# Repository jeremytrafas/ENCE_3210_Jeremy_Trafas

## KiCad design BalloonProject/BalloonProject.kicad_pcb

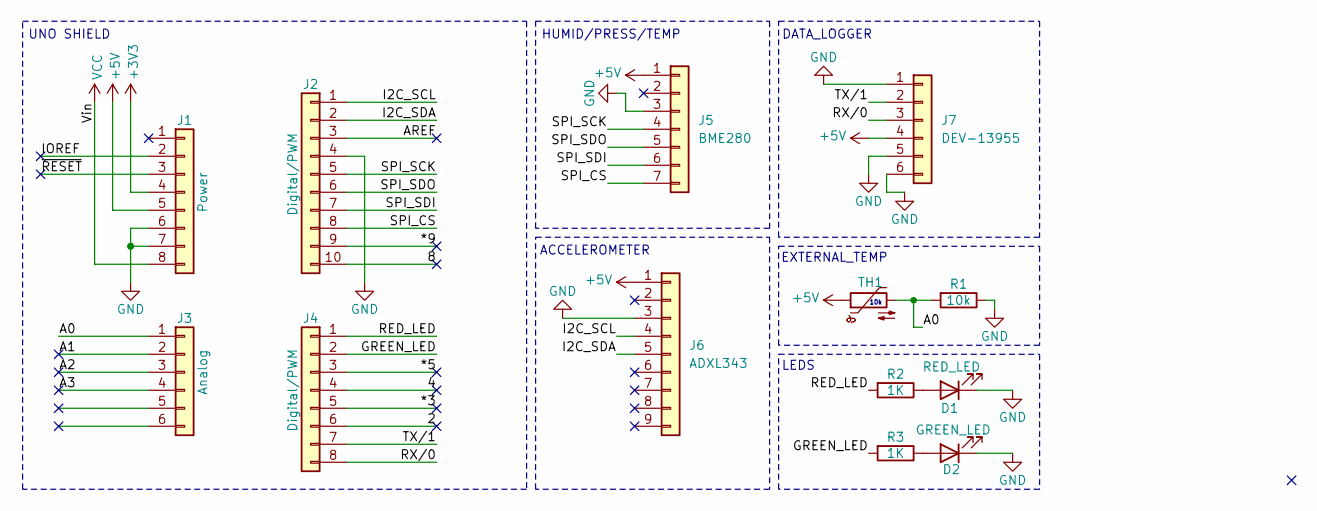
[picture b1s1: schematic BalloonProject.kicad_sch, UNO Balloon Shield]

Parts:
D1: RED_LED; LED_D5.0mm
D2: GREEN_LED; LED_D5.0mm
J1: Power; PinSocket_1x08_P2.54mm_Vertical
J2: Digital/PWM; PinSocket_1x10_P2.54mm_Vertical
J3: Analog; PinSocket_1x06_P2.54mm_Vertical
J4: Digital/PWM; PinSocket_1x08_P2.54mm_Vertical
J5: BME280; PinSocket_1x07_P2.54mm_Vertical
J6: ADXL343; PinSocket_1x09_P2.54mm_Vertical
J7: DEV-13955; PinSocket_1x06_P2.54mm_Vertical
NXRT15XH103FA1B030: TH1; R_Axial_DIN0411_L9.9mm_D3.6mm_P15.24mm_Horizontal
R1: 10k; R_Axial_DIN0411_L9.9mm_D3.6mm_P15.24mm_Horizontal
R2, R3: 1K; R_Axial_DIN0411_L9.9mm_D3.6mm_P15.24mm_Horizontal

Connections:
+3V3: J1.4
+5V: J1.5, J5.1, J6.1, J7.4, NXRT15XH103FA1B030.1
/2: J4.6
/4: J4.4
/8: J2.10
/*3: J4.5
/*5: J4.3
/*9: J2.9
/A0: J3.1, NXRT15XH103FA1B030.2, R1.2
/A1: J3.2
/A2: J3.3
/A3: J3.4
/AREF: J2.3
/GREEN_LED: J4.2, R3.2
/I2C_SCL: J2.1, J6.4
/I2C_SDA: J2.2, J6.5
/IOREF: J1.2
/RED_LED: J4.1, R2.2
/RX/0: J4.8, J7.3
/SPI_CS: J2.8, J5.7
/SPI_SCK: J2.5, J5.4
/SPI_SDI: J2.7, J5.6
/SPI_SDO: J2.6, J5.5
/TX/1: J4.7, J7.2
/~RESET: J1.3
GND: D1.1 (K), D2.1 (K), J1.6, J1.7, J2.4, J5.3, J6.3, J7.1, J7.5, J7.6, R1.1
unnamed: D1.2 (A), R2.1
unnamed: D2.2 (A), R3.1
VCC: J1.8

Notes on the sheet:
10k
ACCELEROMETER
UNO SHIELD
LEDS
HUMID/PRESS/TEMP
EXTERNAL_TEMP
DATA_LOGGER

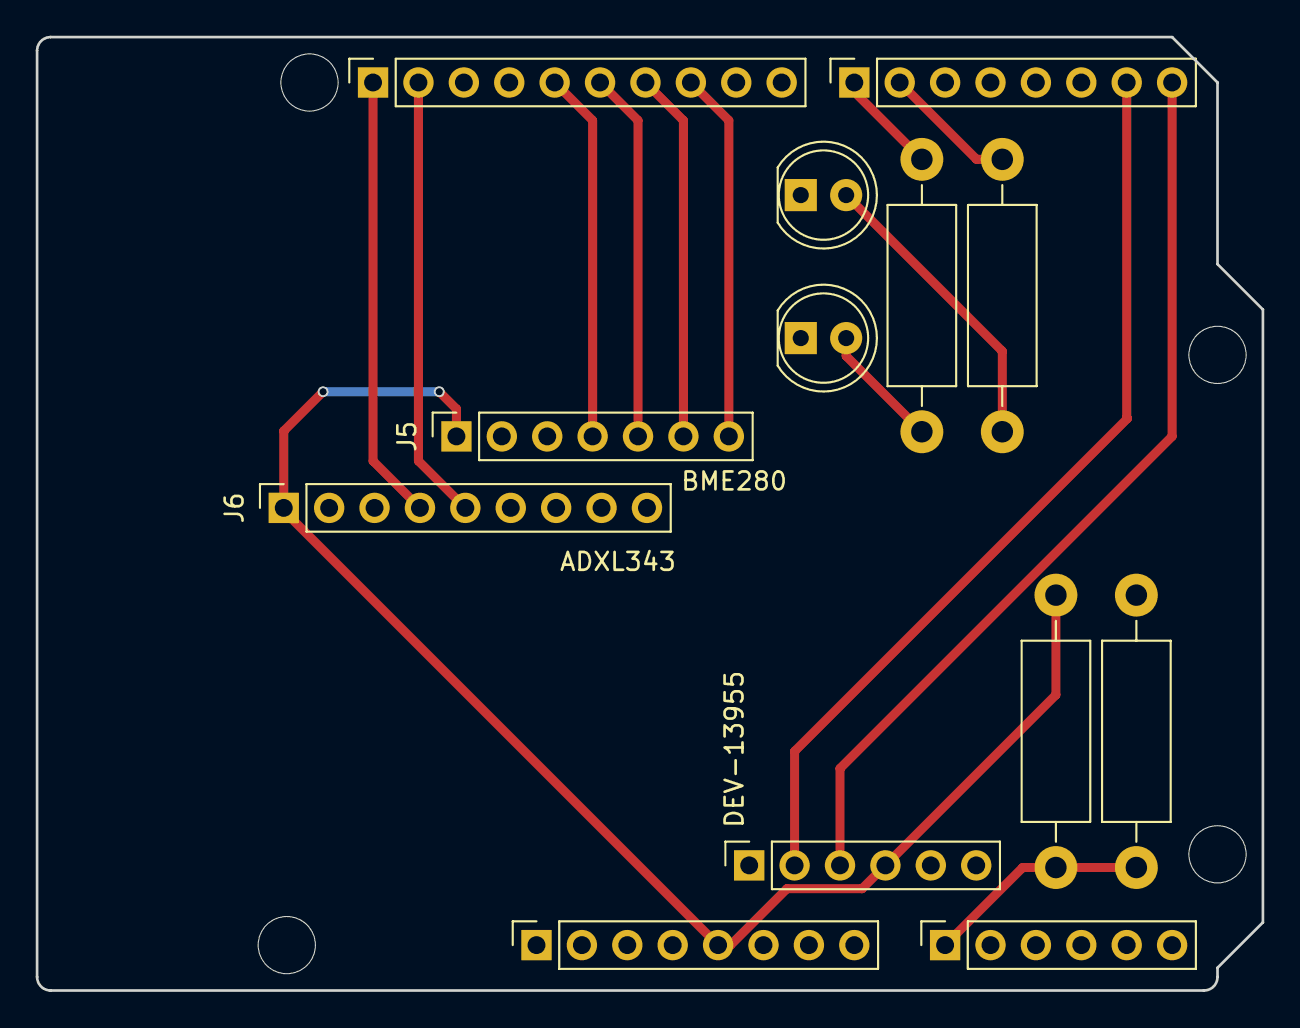
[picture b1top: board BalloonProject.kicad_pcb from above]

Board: 2 copper layers, 68.6 x 53.3 mm, 17 parts (0 on the bottom side), 15 nets.

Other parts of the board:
MH1, MH2, MH3, MH4: MountingHole_3.2mm

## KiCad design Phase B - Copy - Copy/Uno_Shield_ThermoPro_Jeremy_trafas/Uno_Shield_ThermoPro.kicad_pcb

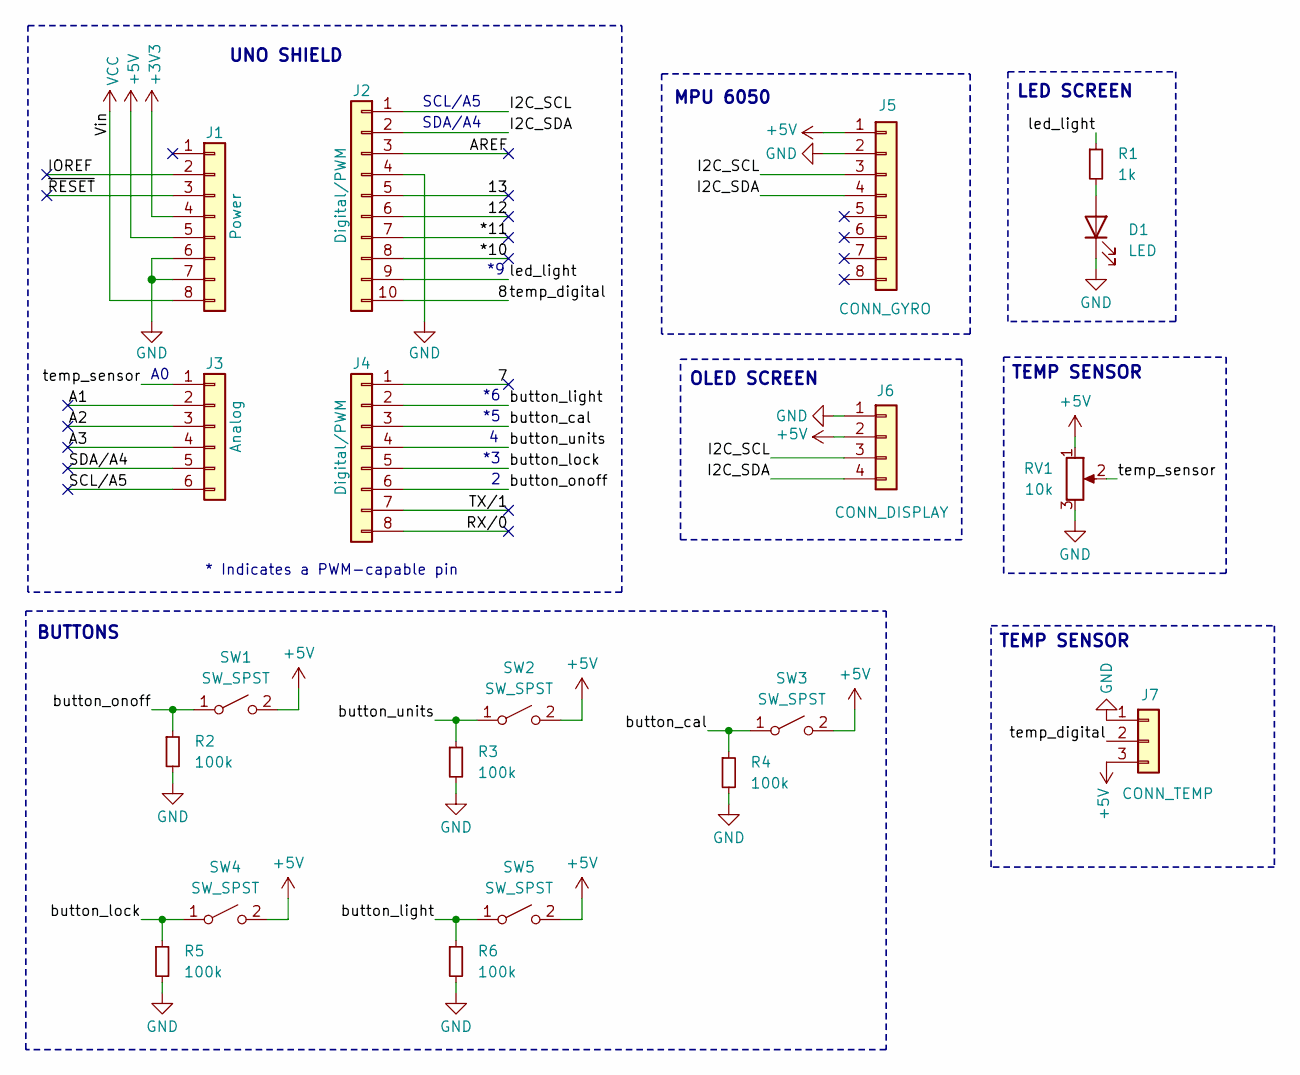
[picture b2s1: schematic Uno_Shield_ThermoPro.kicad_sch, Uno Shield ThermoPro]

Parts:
D1: LED; LED_D5.0mm
J1: Power; PinSocket_1x08_P2.54mm_Vertical
J2: Digital/PWM; PinSocket_1x10_P2.54mm_Vertical
J3: Analog; PinSocket_1x06_P2.54mm_Vertical
J4: Digital/PWM; PinSocket_1x08_P2.54mm_Vertical
J5: CONN_GYRO; PinSocket_1x08_P2.54mm_Vertical
J6: CONN_DISPLAY; PinSocket_1x04_P2.54mm_Vertical
J7: CONN_TEMP; JST_XH_B3B-XH-A_1x03_P2.50mm_Vertical
R1: 1k; R_Axial_DIN0411_L9.9mm_D3.6mm_P15.24mm_Horizontal
R2, R3, R4, R5, R6: 100k; R_Axial_DIN0411_L9.9mm_D3.6mm_P15.24mm_Horizontal
RV1: 10k; Potentiometer_Bourns_3386P_Vertical
SW1, SW2, SW3, SW4, SW5: SW_SPST; SW_PUSH_6mm

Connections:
+3V3: J1.4
+5V: J1.5, J5.1, J6.2, J7.3, RV1.1, SW1.2 (B), SW2.2 (B), SW3.2 (B), SW4.2 (B), SW5.2 (B)
/7: J4.1
/8: J2.10, J7.2
/12: J2.6
/13: J2.5
/*10: J2.8
/*11: J2.7
/A1: J3.2
/A2: J3.3
/A3: J3.4
/AREF: J2.3
/I2C_SCL: J2.1, J5.3, J6.3
/I2C_SDA: J2.2, J5.4, J6.4
/IOREF: J1.2
/RX/0: J4.8
/SCL/A5: J3.6
/SDA/A4: J3.5
/TX/1: J4.7
/button_cal: J4.3, R4.1, SW3.1 (A)
/button_light: J4.2, R6.1, SW5.1 (A)
/button_lock: J4.5, R5.1, SW4.1 (A)
/button_onoff: J4.6, R2.1, SW1.1 (A)
/button_units: J4.4, R3.1, SW2.1 (A)
/led_light: J2.9, R1.1
/temp_sensor: J3.1, RV1.2
/~RESET: J1.3
GND: D1.1 (K), J1.6, J1.7, J2.4, J5.2, J6.1, J7.1, R2.2, R3.2, R4.2, R5.2, R6.2, RV1.3
unnamed: D1.2 (A), R1.2
VCC: J1.8

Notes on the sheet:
OLED SCREEN
TEMP SENSOR
LED SCREEN
UNO SHIELD
MPU 6050
SCL/A5
SDA/A4
BUTTONS
* Indicates a PWM-capable pin

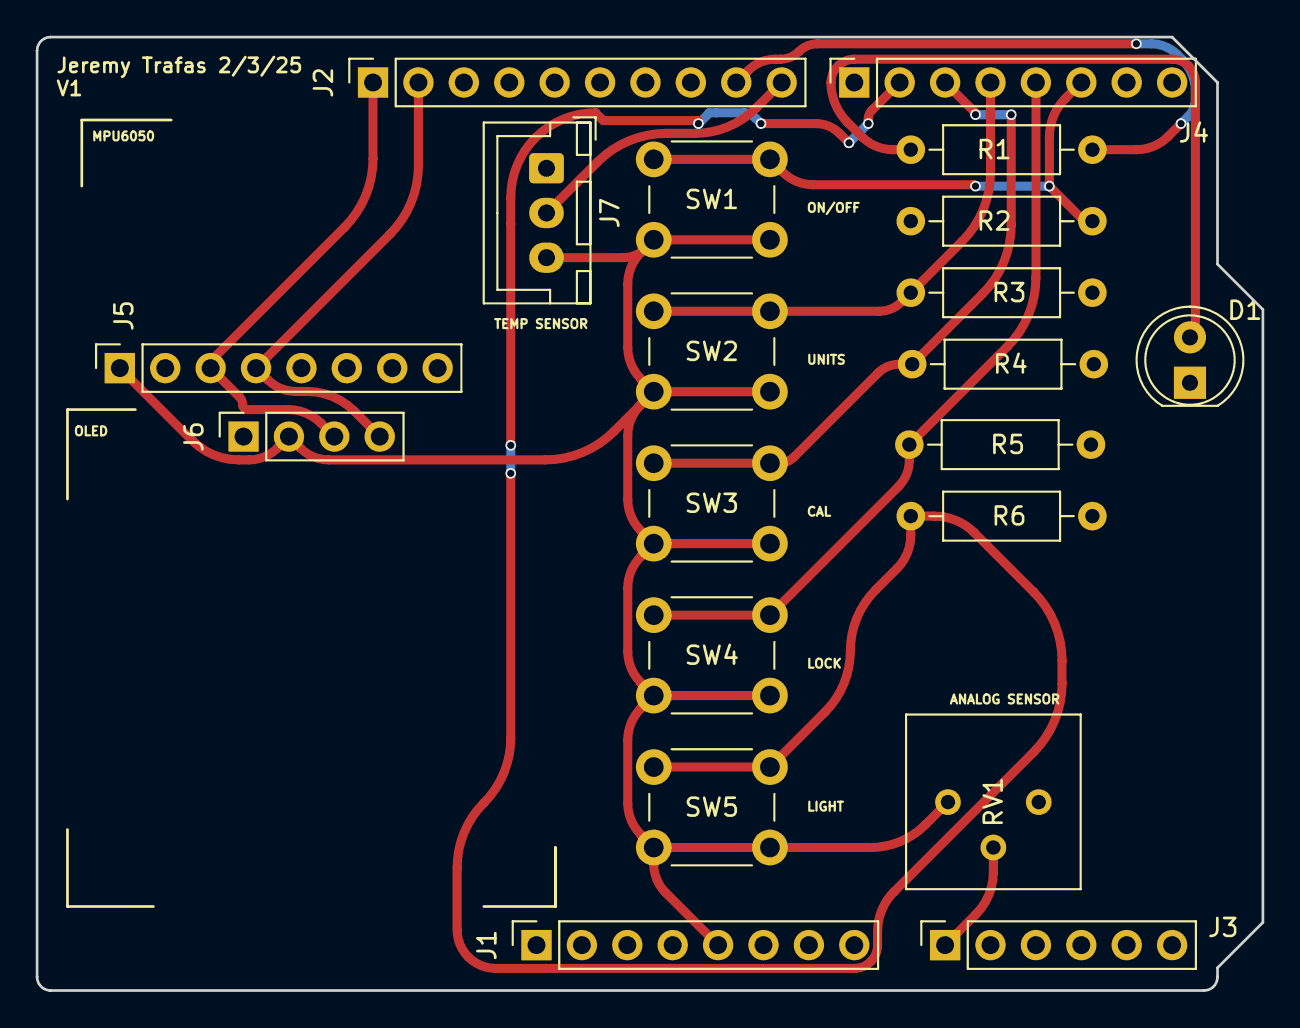
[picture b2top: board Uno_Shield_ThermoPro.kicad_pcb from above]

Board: 2 copper layers, 68.6 x 53.3 mm, 20 parts (0 on the bottom side), 13 nets.

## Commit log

2025-01-10 Lab 1 prob 2-4
2025-01-16 Rest of problems
2025-01-17 Forgot prob 1
2025-01-17 Lab 2 prob 1-3
2025-01-17 Last prob
2025-01-27 Lab 3
2025-01-31 Phase B
2025-01-31 Phase B try 2
2025-01-31 phase 2
2025-02-03 Update PCB
2025-02-04 Fixed PCB
2025-02-21 Lab4 complete
2025-02-25 ThermoPro code
2025-03-12 Balloon Project
